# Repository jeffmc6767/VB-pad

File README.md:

This is a volume/brightness controler for your personal device. 
-
It has 2 rotary encoders for volume and brightness control and a 0.91 inch OLED for whatever you want to see. There are also 3 customizable key switches for shortcuts or anything you want. 

I used fusion360 and kicad to design everything. 

Image gallery:
-
- PCB schematic:

- Completed PCB:

- Top of case:

- Parts of the case:

BOM:
-

1. 1x PCB
2. 1x Seeed XIAO RP2040 Microcontroller
3. 3x Cherry MX Switches
4. 2x EC11 Encoder with switch
5.  3x white blank DSA keycaps
6.  1x 3D printed case(I have 3d printer)
7.  4x M3x16mm screws
8.  4x M3x5mx4mm heatset inserts

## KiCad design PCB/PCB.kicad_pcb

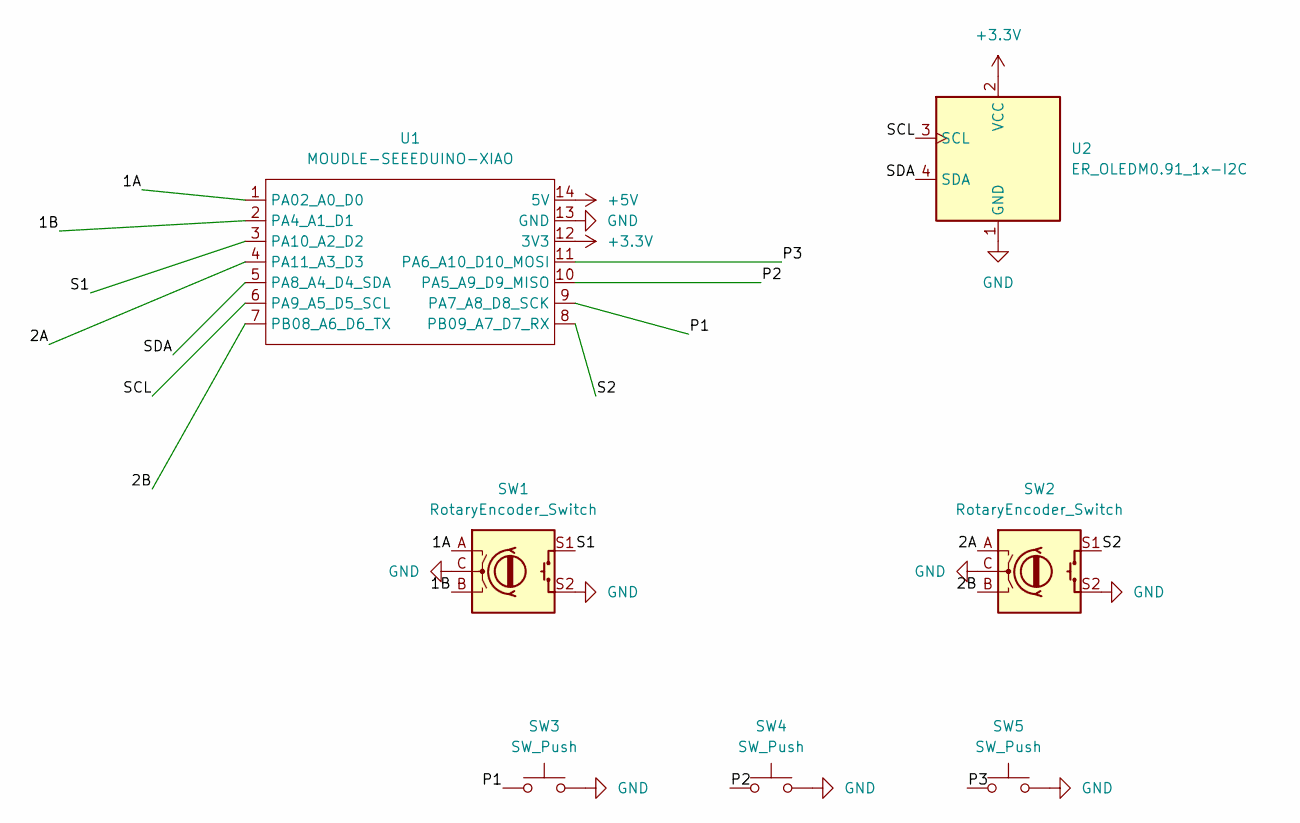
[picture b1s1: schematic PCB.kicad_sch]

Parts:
SW1, SW2: RotaryEncoder_Switch; RotaryEncoder_Alps_EC11E-Switch_Vertical_H20mm
SW3, SW4, SW5: SW_Push; SW_Cherry_MX_1.00u_PCB
U1: MOUDLE-SEEEDUINO-XIAO; XIAO-Generic-Hybrid-14P-2.54-21X17.8MM
U2: ER_OLEDM0.91_1x-I2C

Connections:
+3.3V: U1.12 (3V3), U2.2 (VCC)
+5V: U1.14 (5V)
/1A: SW1.A, U1.1 (PA02_A0_D0)
/1B: SW1.B, U1.2 (PA4_A1_D1)
/2A: SW2.A, U1.4 (PA11_A3_D3)
/2B: SW2.B, U1.7 (PB08_A6_D6_TX)
/P1: SW3.1, U1.9 (PA7_A8_D8_SCK)
/P2: SW4.1, U1.10 (PA5_A9_D9_MISO)
/P3: SW5.1, U1.11 (PA6_A10_D10_MOSI)
/S1: SW1.S1, U1.3 (PA10_A2_D2)
/S2: SW2.S1, U1.8 (PB09_A7_D7_RX)
/SCL: U1.6 (PA9_A5_D5_SCL), U2.3 (SCL)
/SDA: U1.5 (PA8_A4_D4_SDA), U2.4 (SDA)
GND: SW1.C, SW1.S2, SW2.C, SW2.S2, SW3.2, SW4.2, SW5.2, U1.13 (GND), U2.1 (GND)

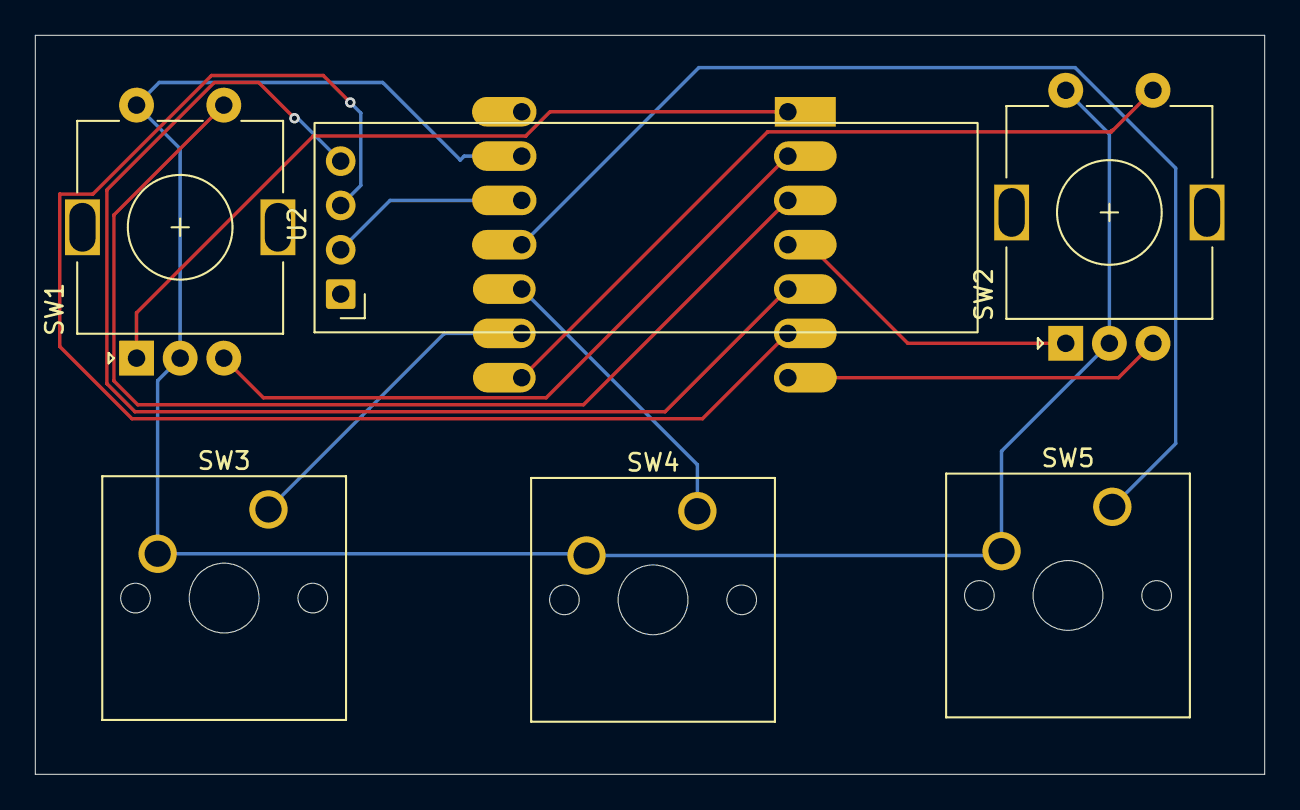
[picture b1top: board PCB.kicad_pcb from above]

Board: 2 copper layers, 70.4 x 42.4 mm, 7 parts (1 on the bottom side), 13 nets.
